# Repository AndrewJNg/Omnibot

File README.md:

# Omnibot
Mecanum (Omniwheel) wheel robot capable of all directional movement

Omnibot pinout

36.	 encoder	
39.	 encoder	
34.	 encoder	
35.	 encoder	
32.	 Battery monitor	
33.		
25.	 PWMA	(Left motors)
26.	 AIN2	
27.	 AIN1	
14.	 BIN1	
12.	 BIN2	
13.	 PWMB	
			
23.	 MPU6050	
22.	 	SCL
1.		
3.		
21.	 	SDA
19.		
18.		
5.	 PWMA	(Right motors)
17.	 AIN2	
16.	 AIN1	
4.	 BIN1	
2.	 BIN2	
15.	 PWMB

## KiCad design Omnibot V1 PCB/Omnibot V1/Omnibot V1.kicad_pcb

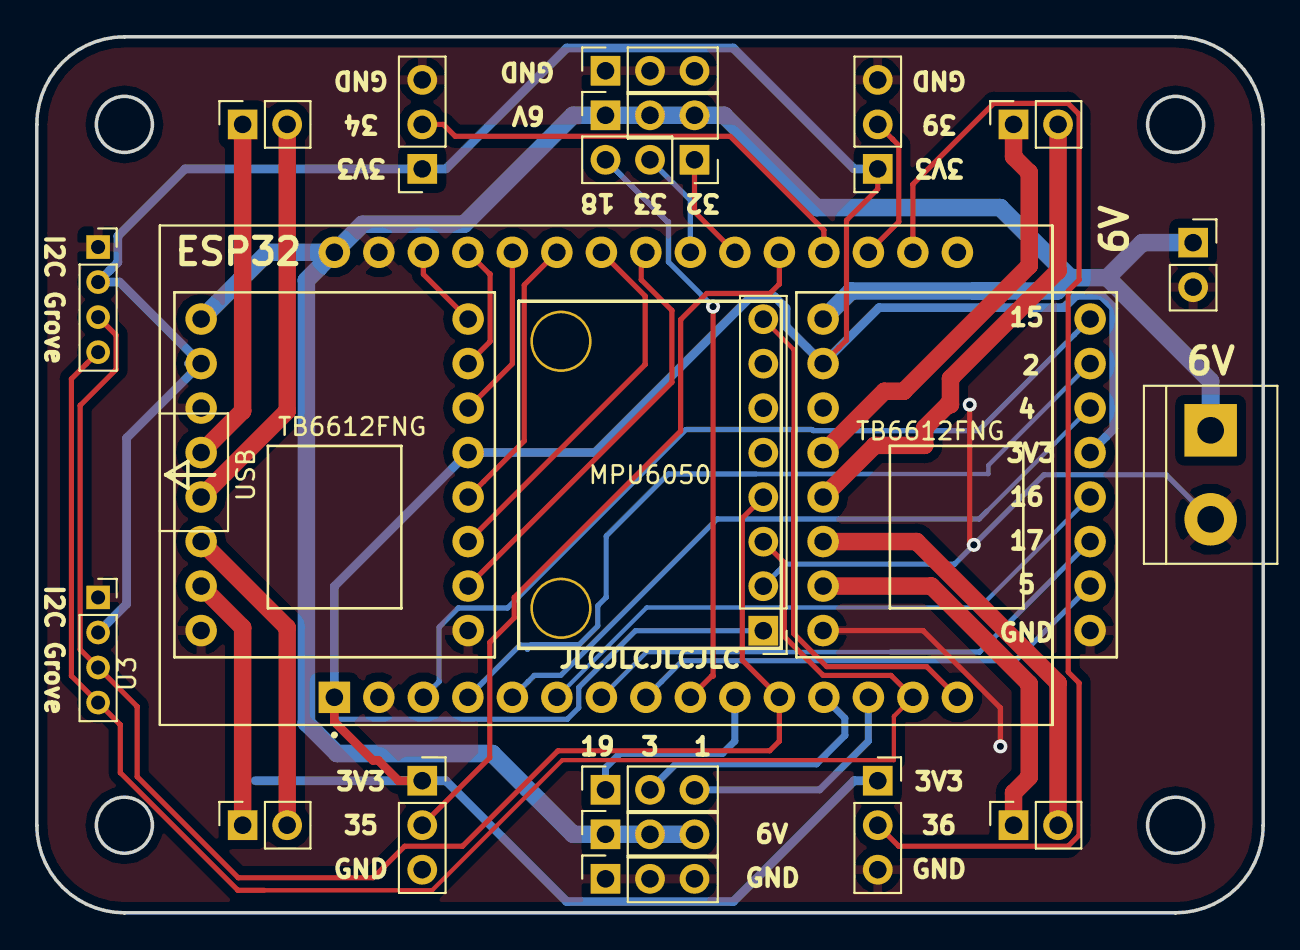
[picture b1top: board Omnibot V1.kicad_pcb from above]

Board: 2 copper layers, 70.0 x 50.0 mm, 22 parts (0 on the bottom side), 36 nets.

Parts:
J1, J8: I2C Grove; PinSocket_1x04_P2.00mm_Vertical
J2: TL Encoder; PinSocket_1x03_P2.54mm_Vertical
J3: TR Encoder; PinSocket_1x03_P2.54mm_Vertical
J4: BL Encoder; PinSocket_1x03_P2.54mm_Vertical
J5: BR Encoder; PinSocket_1x03_P2.54mm_Vertical
J6: 6V; TerminalBlock_bornier-2_P5.08mm
J7: 6V; PinSocket_1x02_P2.54mm_Vertical
J9, J10: Conn_01x03_Male; PinSocket_1x03_P2.54mm_Vertical
J11, J13: 6v; PinSocket_1x03_P2.54mm_Vertical
J12, J14: GND; PinSocket_1x03_P2.54mm_Vertical
M1, M2, M3, M4: Motor_DC; PinSocket_1x02_P2.54mm_Vertical
U1, U2: TB6612FNG
U3: ESP32-WROOM; MODULE_ESP32_DEVKIT_V1
U4: MPU-6050; MPU6050 module

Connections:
1: J10.3, U3.35
2: U1.22, U3.24
3: J10.2, U3.34
4: U1.21, U3.26
5: U1.15, U3.29
12: U2.22, U3.14
13: U2.23, U3.16
14: U2.21, U3.13
15: U1.23, U3.23
16: U1.17, U3.27
17: U1.16, U3.28
18: J9.3, U3.30
19: J10.1, U3.31
21_SDA: J1.3, J8.3, U3.33, U4.24
22_SCL: J1.4, J8.4, U3.36, U4.23
23: U3.37, U4.12
25: U2.15, U3.10
26: U2.16, U3.11
27: U2.17, U3.12
32: J9.1, U3.8
33: J9.2, U3.9
34: J3.2, U3.6
35: J2.2, U3.7
36: J4.2, U3.4
39: J5.2, U3.5
+3V3: J1.2, J2.1, J3.1, J4.1, J5.1, J8.2, U1.19, U1.20, U2.19, U2.20, U3.2, U4.13
GND: J1.1, J2.3, J3.3, J4.3, J5.3, J6.2, J7.2, J8.1, J12.1, J12.2, J12.3, J14.1, J14.2, J14.3, U1.4, U1.9, U1.18, U2.4, U2.9, U2.18, U3.15, U4.18
unnamed: M1.1, U2.1
unnamed: M1.2, U2.5
unnamed: M2.1, U2.11
unnamed: M2.2, U2.7
unnamed: M3.1, U1.1
unnamed: M3.2, U1.5
unnamed: M4.1, U1.11
unnamed: M4.2, U1.7
VCC: J6.1, J7.1, J11.1, J11.2, J11.3, J13.1, J13.2, J13.3, U1.14, U2.14, U3.32

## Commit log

2022-01-04 added ros node version of Omniwheel robot V1
2022-01-04 made some changes to the ros file
2022-01-23 Added OTA (over the air upload)
2022-01-24 Create README.md
    added readme file
2022-01-24 changes setup file to allow ps3 to connect
2022-01-24 added pinout list to readme
2022-01-24 changed styling format for readme
2022-01-24 made changes to format in readme
2022-12-16 added in PCB design files
